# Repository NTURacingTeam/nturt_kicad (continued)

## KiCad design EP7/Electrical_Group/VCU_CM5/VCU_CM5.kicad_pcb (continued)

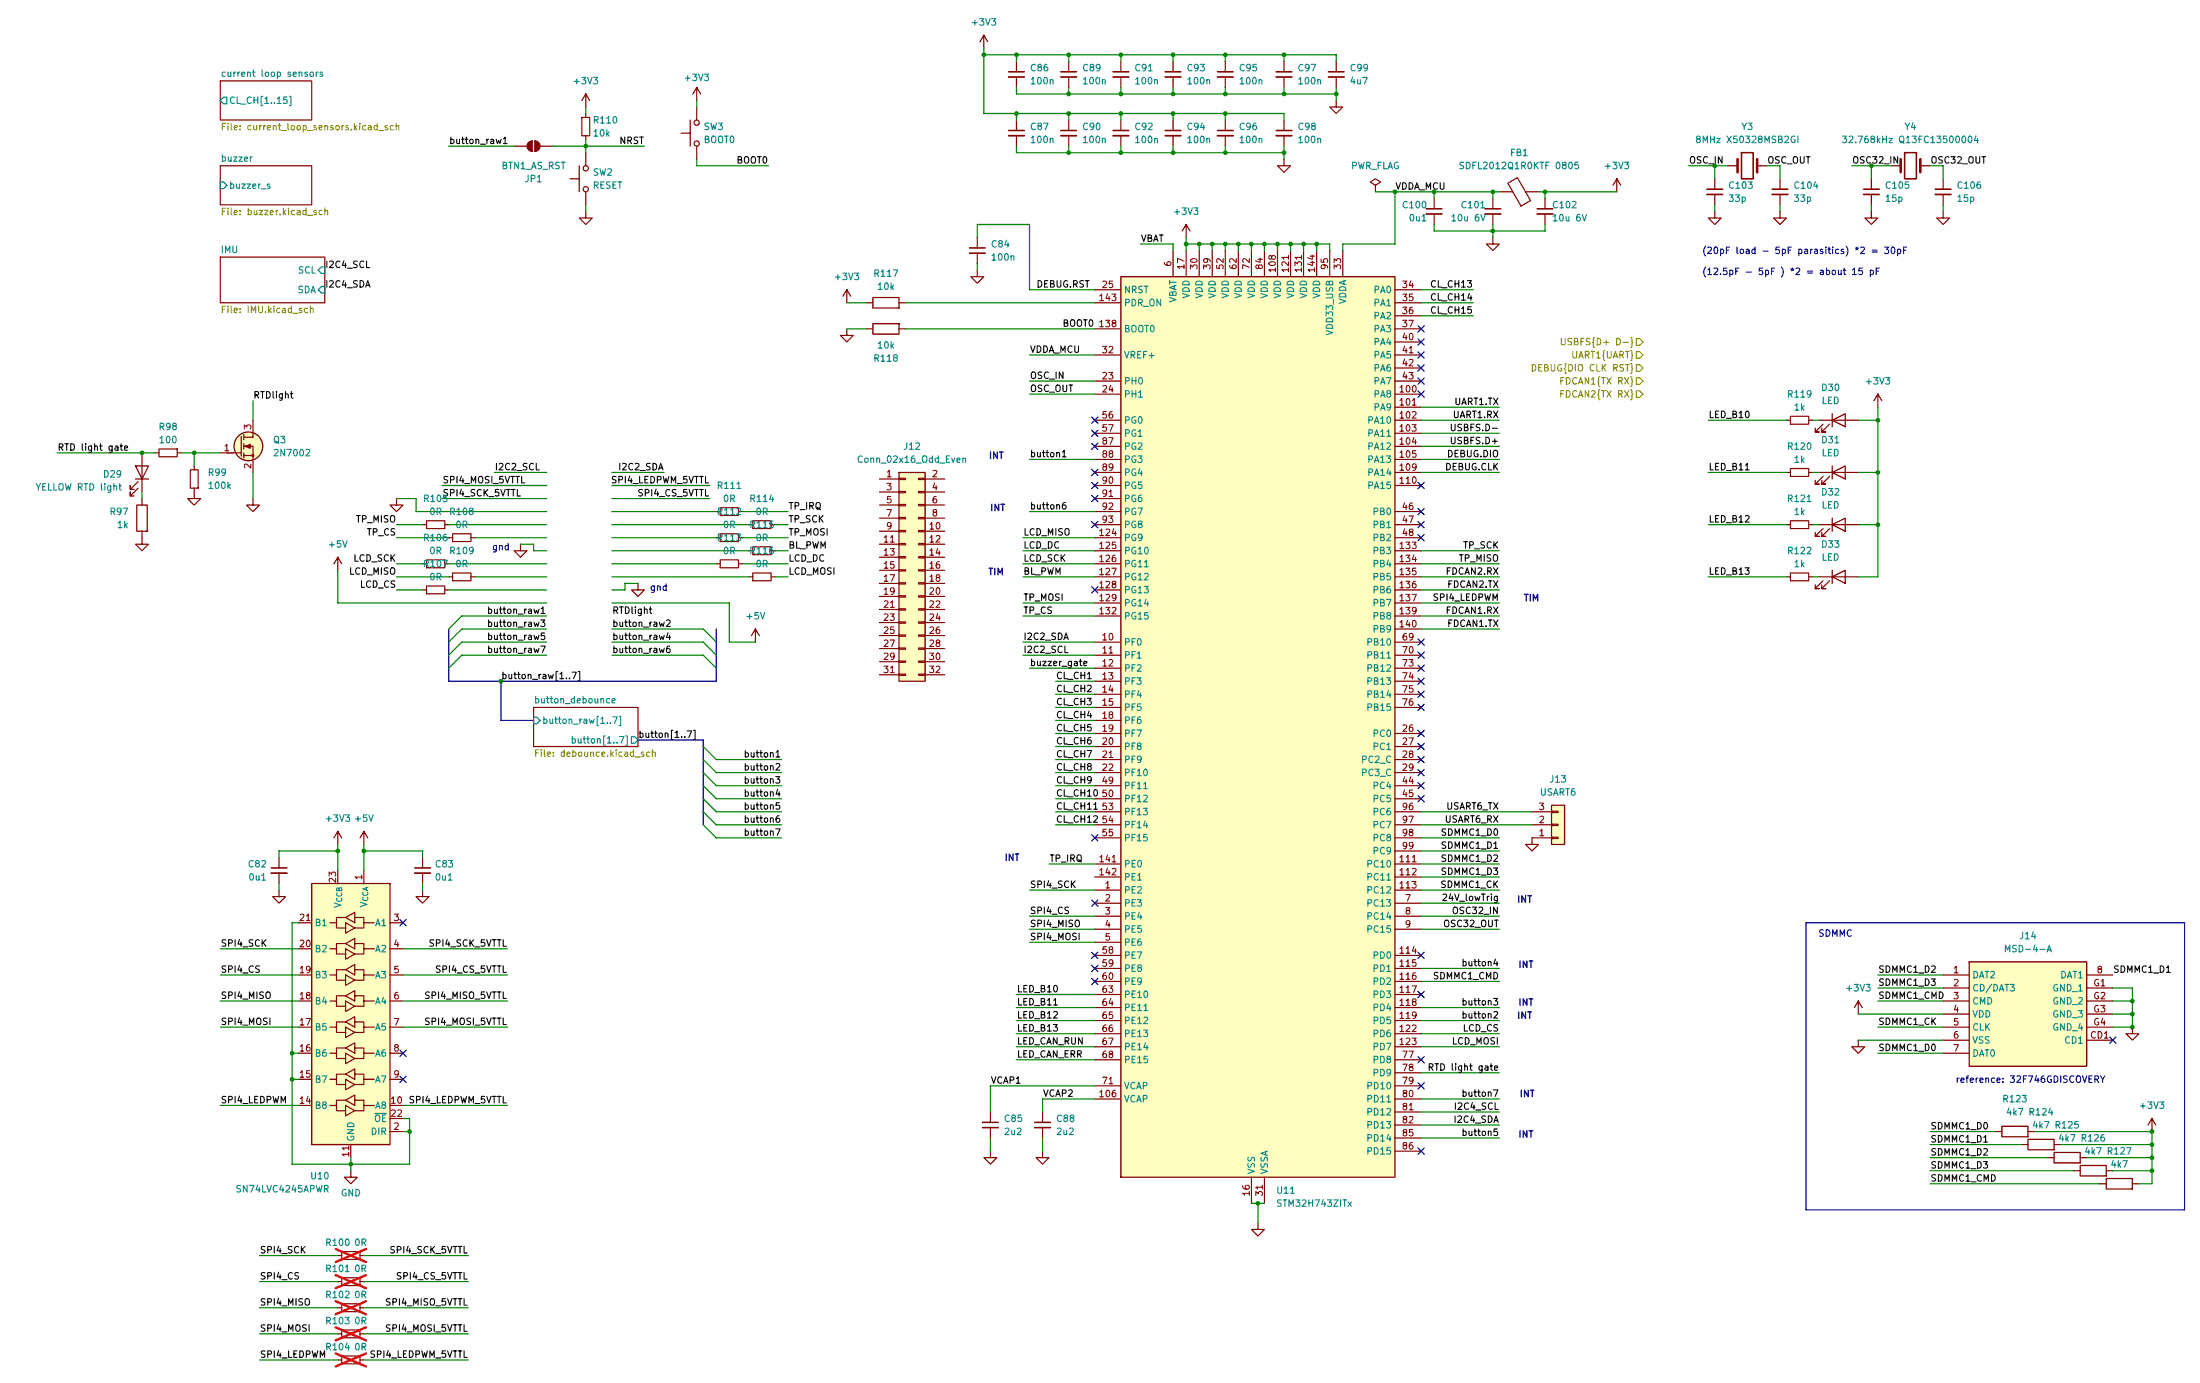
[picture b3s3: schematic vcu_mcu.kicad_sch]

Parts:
C82, C83, C100: 0u1; C_0402_1005Metric
C84, C86, C87, C89, C90, C91, C92, C93, C94, C95, C96, C97, C98: 100n; C_0402_1005Metric
C85, C88: 2u2; C_0402_1005Metric
C99: 4u7; C_0402_1005Metric
C101, C102: 10u 6V; C_0402_1005Metric
C103, C104: 33p; C_0402_1005Metric
C105, C106: 15p; C_0402_1005Metric
D29: YELLOW RTD light; LED_0603_1608Metric
D30, D31, D32, D33: LED; LED_0603_1608Metric
FB1: SDFL2012Q1R0KTF 0805; L_0805_2012Metric
J12: Conn_02x16_Odd_Even; PinSocket_2x16_P2.00mm_Vertical
J13: USART6; JST_PH_B3B-PH-K_1x03_P2.00mm_Vertical
J14: MSD-4-A; MSD4A; Mouser Part Number 179-MSD-4-A
JP1: BTN1_AS_RST; SolderJumper-2_P1.3mm_Open_RoundedPad1.0x1.5mm
Q3: 2N7002; SOT-23
R97, R119, R120, R121, R122: 1k; R_0402_1005Metric
R98: 100; R_0402_1005Metric
R99: 100k; R_0402_1005Metric
R100, R101, R102, R103, R104: 0R; R_0603_1608Metric_Pad0.98x0.95mm_HandSolder; not fitted
R105, R106, R107, R108, R109, R111, R112, R113, R114, R115, R116: 0R; R_0402_1005Metric
R110, R117, R118: 10k; R_0402_1005Metric
R123, R124, R125, R126, R127: 4k7; R_0402_1005Metric
SW2: RESET; SW_Tactile_SPST_NO_Straight_CK_PTS636Sx25SMTRLFS
SW3: BOOT0; SW_Tactile_SPST_NO_Straight_CK_PTS636Sx25SMTRLFS
U10: SN74LVC4245APWR; TSSOP-24_4.4x7.8mm_P0.65mm
U11: STM32H743ZITx; LQFP-144_20x20mm_P0.5mm
Y3: 8MHz X50328MSB2GI; Crystal_SMD_5032-2Pin_5.0x3.2mm
Y4: 32.768kHz Q13FC13500004; Crystal_SMD_3215-2Pin_3.2x1.5mm

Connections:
+3V3: C82.1, C86.1, C87.1, C89.1, C90.1, C91.1, C92.1, C93.1, C94.1, C95.1, C96.1, C97.1, C98.1, C99.1, C102.1, D30.2 (A), D31.2 (A), D32.2 (A), D33.2 (A), FB1.1, J14.4 (VDD), R110.1, R117.1, R123.2, R124.2, R125.2, R126.2, R127.2, SW3.2, U10.23 (V_{CCB}), U10.24 (V_{CCB}), U11.17 (VDD), U11.30 (VDD), U11.39 (VDD), U11.52 (VDD), U11.62 (VDD), U11.72 (VDD), U11.84 (VDD), U11.95 (VDD33_USB), U11.108 (VDD), U11.121 (VDD), U11.131 (VDD), U11.144 (VDD); also elsewhere on the board
+5V: C83.1, U10.1 (V_{CCA}); also elsewhere on the board
/CAN 1/CAN.RX: U11.139 (PB8); also elsewhere on the board
/CAN 1/CAN.TX: U11.140 (PB9); also elsewhere on the board
/CAN 2/CAN.RX: U11.135 (PB5); also elsewhere on the board
/CAN 2/CAN.TX: U11.136 (PB6); also elsewhere on the board
/DFP1.D+: U11.104 (PA12); also elsewhere on the board
/DFP1.D-: U11.103 (PA11); also elsewhere on the board
/stlink/DEBUG.CLK: U11.109 (PA14); also elsewhere on the board
/stlink/DEBUG.DIO: U11.105 (PA13); also elsewhere on the board
/stlink/DEBUG.RST: C84.1, U11.25 (NRST); also elsewhere on the board
/stlink/VCP_MCU.RX: U11.102 (PA10); also elsewhere on the board
/stlink/VCP_MCU.TX: U11.101 (PA9); also elsewhere on the board
/vcu mcu/24V_lowTrig: U11.7 (PC13)
/vcu mcu/BL_PWM: R115.2, U11.127 (PG12)
/vcu mcu/BOOT0: R118.2, SW3.1, U11.138 (BOOT0)
/vcu mcu/I2C2_SCL: U11.11 (PF1)
/vcu mcu/I2C2_SDA: U11.10 (PF0)
/vcu mcu/I2C4_SCL: U11.81 (PD12); also elsewhere on the board
/vcu mcu/I2C4_SDA: U11.82 (PD13); also elsewhere on the board
/vcu mcu/LCD_CS: R107.1, U11.122 (PD6)
/vcu mcu/LCD_DC: R113.2, U11.125 (PG10)
/vcu mcu/LCD_MISO: R109.1, U11.124 (PG9)
/vcu mcu/LCD_MOSI: R116.2, U11.123 (PD7)
/vcu mcu/LCD_SCK: R106.1, U11.126 (PG11)
/vcu mcu/LED_B10: R119.1, U11.63 (PE10)
/vcu mcu/LED_B11: R120.1, U11.64 (PE11)
/vcu mcu/LED_B12: R121.1, U11.65 (PE12)
/vcu mcu/LED_B13: R122.1, U11.66 (PE13)
/vcu mcu/LED_CAN_ERR: U11.68 (PE15)
/vcu mcu/LED_CAN_RUN: U11.67 (PE14)
/vcu mcu/NRST: JP1.1 (A), R110.2, SW2.2
/vcu mcu/OSC32_IN: C105.1, U11.8 (PC14), Y4.1
/vcu mcu/OSC32_OUT: C106.1, U11.9 (PC15), Y4.2
/vcu mcu/OSC_IN: C103.1, U11.23 (PH0), Y3.1
/vcu mcu/OSC_OUT: C104.1, U11.24 (PH1), Y3.2
/vcu mcu/RTD light gate: D29.2 (A), R98.2, U11.78 (PD9)
/vcu mcu/RTDlight: Q3.3 (D)
/vcu mcu/SDMMC1_CK: J14.5 (CLK), U11.113 (PC12)
/vcu mcu/SDMMC1_CMD: J14.3 (CMD), R127.1, U11.116 (PD2)
/vcu mcu/SDMMC1_D0: J14.7 (DAT0), R123.1, U11.98 (PC8)
/vcu mcu/SDMMC1_D1: J14.8 (DAT1), R124.1, U11.99 (PC9)
/vcu mcu/SDMMC1_D2: J14.1 (DAT2), R125.1, U11.111 (PC10)
/vcu mcu/SDMMC1_D3: J14.2 (CD/DAT3), R126.1, U11.112 (PC11)
/vcu mcu/SPI4_CS: R101.1, U10.19 (B3), U11.3 (PE4)
/vcu mcu/SPI4_CS_5VTTL: R101.2, U10.5 (A3)
/vcu mcu/SPI4_LEDPWM: R104.1, U10.14 (B8), U11.137 (PB7)
/vcu mcu/SPI4_LEDPWM_5VTTL: R104.2, U10.10 (A8)
/vcu mcu/SPI4_MISO: R102.1, U10.18 (B4), U11.4 (PE5)
/vcu mcu/SPI4_MISO_5VTTL: R102.2, U10.6 (A4)
/vcu mcu/SPI4_MOSI: R103.1, U10.17 (B5), U11.5 (PE6)
/vcu mcu/SPI4_MOSI_5VTTL: R103.2, U10.7 (A5)
/vcu mcu/SPI4_SCK: R100.1, U10.20 (B2), U11.1 (PE2)
/vcu mcu/SPI4_SCK_5VTTL: R100.2, U10.4 (A2)
/vcu mcu/TP_CS: R108.1, U11.132 (PG15)
/vcu mcu/TP_IRQ: R111.1, U11.141 (PE0)
/vcu mcu/TP_MISO: R105.1, U11.134 (PB4)
/vcu mcu/TP_MOSI: R112.2, U11.129 (PG14)
/vcu mcu/TP_SCK: R114.2, U11.133 (PB3)
/vcu mcu/USART6_RX: J13.2, U11.97 (PC7)
/vcu mcu/USART6_TX: J13.3, U11.96 (PC6)
/vcu mcu/VBAT: U11.6 (VBAT)
/vcu mcu/VCAP1: C85.1, U11.71 (VCAP)
/vcu mcu/VCAP2: C88.1, U11.106 (VCAP)
/vcu mcu/VDDA_MCU: C100.1, C101.1, FB1.2, U11.32 (VREF+), U11.33 (VDDA)
/vcu mcu/button1: U11.88 (PG3); also elsewhere on the board
/vcu mcu/button2: U11.119 (PD5); also elsewhere on the board
/vcu mcu/button3: U11.118 (PD4); also elsewhere on the board
/vcu mcu/button4: U11.115 (PD1); also elsewhere on the board
/vcu mcu/button5: U11.85 (PD14); also elsewhere on the board
/vcu mcu/button6: U11.92 (PG7); also elsewhere on the board
/vcu mcu/button7: U11.80 (PD11); also elsewhere on the board
/vcu mcu/button_raw1: JP1.2 (B); also elsewhere on the board
/vcu mcu/buzzer_gate: U11.12 (PF2)
/vcu mcu/current loop sensors/CL_CH1: U11.13 (PF3); also elsewhere on the board
/vcu mcu/current loop sensors/CL_CH2: U11.14 (PF4); also elsewhere on the board
/vcu mcu/current loop sensors/CL_CH3: U11.15 (PF5); also elsewhere on the board
/vcu mcu/current loop sensors/CL_CH4: U11.18 (PF6); also elsewhere on the board
/vcu mcu/current loop sensors/CL_CH5: U11.19 (PF7); also elsewhere on the board
/vcu mcu/current loop sensors/CL_CH6: U11.20 (PF8); also elsewhere on the board
/vcu mcu/current loop sensors/CL_CH7: U11.21 (PF9); also elsewhere on the board
/vcu mcu/current loop sensors/CL_CH8: U11.22 (PF10); also elsewhere on the board
/vcu mcu/current loop sensors/CL_CH9: U11.49 (PF11); also elsewhere on the board
/vcu mcu/current loop sensors/CL_CH10: U11.50 (PF12); also elsewhere on the board
/vcu mcu/current loop sensors/CL_CH11: U11.53 (PF13); also elsewhere on the board
/vcu mcu/current loop sensors/CL_CH12: U11.54 (PF14); also elsewhere on the board
/vcu mcu/current loop sensors/CL_CH13: U11.34 (PA0); also elsewhere on the board
/vcu mcu/current loop sensors/CL_CH14: U11.35 (PA1); also elsewhere on the board
/vcu mcu/current loop sensors/CL_CH15: U11.36 (PA2); also elsewhere on the board
GND: C82.2, C83.2, C84.2, C85.2, C86.2, C87.2, C88.2, C89.2, C90.2, C91.2, C92.2, C93.2, C94.2, C95.2, C96.2, C97.2, C98.2, C99.2, C100.2, C101.2, C102.2, C103.2, C104.2, C105.2, C106.2, J13.1, J14.6 (VSS), J14.G1 (GND_1), J14.G2 (GND_2), J14.G3 (GND_3), J14.G4 (GND_4), Q3.2 (S), R97.2, R99.1, R118.1, SW2.1, U10.2 (DIR), U10.11 (GND), U10.12 (GND), U10.13 (GND), U10.15 (B7), U10.16 (B6), U10.21 (B1), U10.22 (~OE), U11.16 (VSS), U11.31 (VSSA), U11.38 (VSS), U11.51 (VSS), U11.61 (VSS), U11.83 (VSS), U11.94 (VSS), U11.107 (VSS), U11.120 (VSS), U11.130 (VSS); also elsewhere on the board
unnamed: D29.1 (K), R97.1
unnamed: D30.1 (K), R119.2
unnamed: D31.1 (K), R120.2
unnamed: D32.1 (K), R121.2
unnamed: D33.1 (K), R122.2
unnamed: Q3.1 (G), R98.1, R99.2
unnamed: R117.2, U11.143 (PDR_ON)

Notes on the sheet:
gnd
SDMMC
TIM
(20pF load - 5pF parasitics) *2 = 30pF (12.5pF - 5pF ) *2 = about 15 pF
INT
reference: 32F746GDISCOVERY

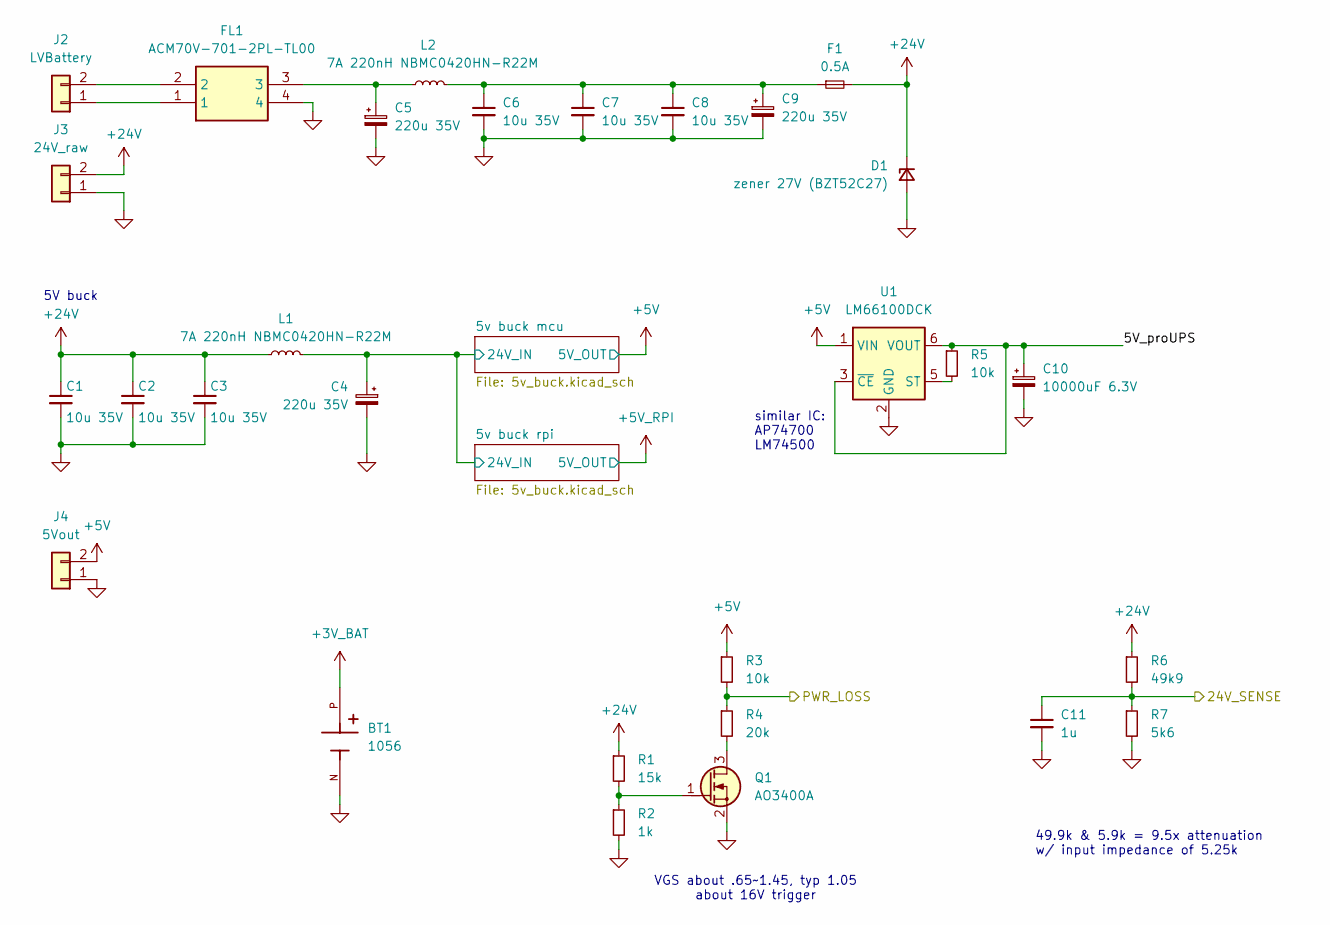
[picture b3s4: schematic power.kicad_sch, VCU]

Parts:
BT1: 1056; BAT_1056; PARTREV D
C1, C2, C3, C6, C7, C8: 10u 35V; C_1206_3216Metric
C4, C5, C9: 220u 35V; CP_Radial_D8.0mm_P3.80mm
C10: 10000uF 6.3V; CP_Radial_D10.0mm_P5.00mm
C11: 1u; C_0402_1005Metric
D1: zener 27V (BZT52C27); D_SOD-123
F1: 0.5A; Fuse_1206_3216Metric
FL1: ACM70V-701-2PL-TL00; Common_Mode_Choke_4A_ACM70V7012PLTL00; Mouser Part Number 810-ACM70V7012PLTL00
J2: LVBattery; JST_XH_B2B-XH-A_1x02_P2.50mm_Vertical
J3: 24V_raw; JST_XH_B2B-XH-A_1x02_P2.50mm_Vertical
J4: 5Vout; JST_XH_B2B-XH-A_1x02_P2.50mm_Vertical
L1, L2: 7A 220nH NBMC0420HN-R22M; L_Ferrocore_DLG-0403
Q1: AO3400A; SOT-23
R1: 15k; R_0402_1005Metric
R2: 1k; R_0402_1005Metric
R3, R5: 10k; R_0402_1005Metric
R4: 20k; R_0402_1005Metric
R6: 49k9; R_0402_1005Metric
R7: 5k6; R_0402_1005Metric
U1: LM66100DCK; SOT-363_SC-70-6

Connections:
+3V_BAT: BT1.P; also elsewhere on the board
+5V: J4.2, R3.1, U1.1 (VIN); also elsewhere on the board
+24V: C1.1, C2.1, C3.1, D1.1 (K), F1.2, J3.2, L1.1, R1.1, R6.1; also elsewhere on the board
/power/5V_proUPS: C10.1, R5.1, U1.3 (~CE), U1.6 (VOUT)
/power/5v buck mcu/24V_IN: C4.1, L1.2; also elsewhere on the board
/power/24V_SENSE: C11.1, R6.2, R7.1
/power/PWR_LOSS: R3.2, R4.1
GND: BT1.N, C1.2, C2.2, C3.2, C4.2, C5.2, C6.2, C7.2, C8.2, C9.2, C10.2, C11.2, D1.2 (A), FL1.4, J3.1, J4.1, Q1.2 (S), R2.2, R7.2, U1.2 (GND); also elsewhere on the board
unnamed: C5.1, FL1.3, L2.1
unnamed: C6.1, C7.1, C8.1, C9.1, F1.1, L2.2
unnamed: FL1.1, J2.1
unnamed: FL1.2, J2.2
unnamed: Q1.3 (D), R4.2
unnamed: Q1.1 (G), R1.2, R2.1
unnamed: R5.2, U1.5 (ST)

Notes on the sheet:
similar IC: AP74700 LM74500
5V buck
49.9k & 5.9k = 9.5x attenuation w/ input impedance of 5.25k
VGS about .65~1.45, typ 1.05 about 16V trigger

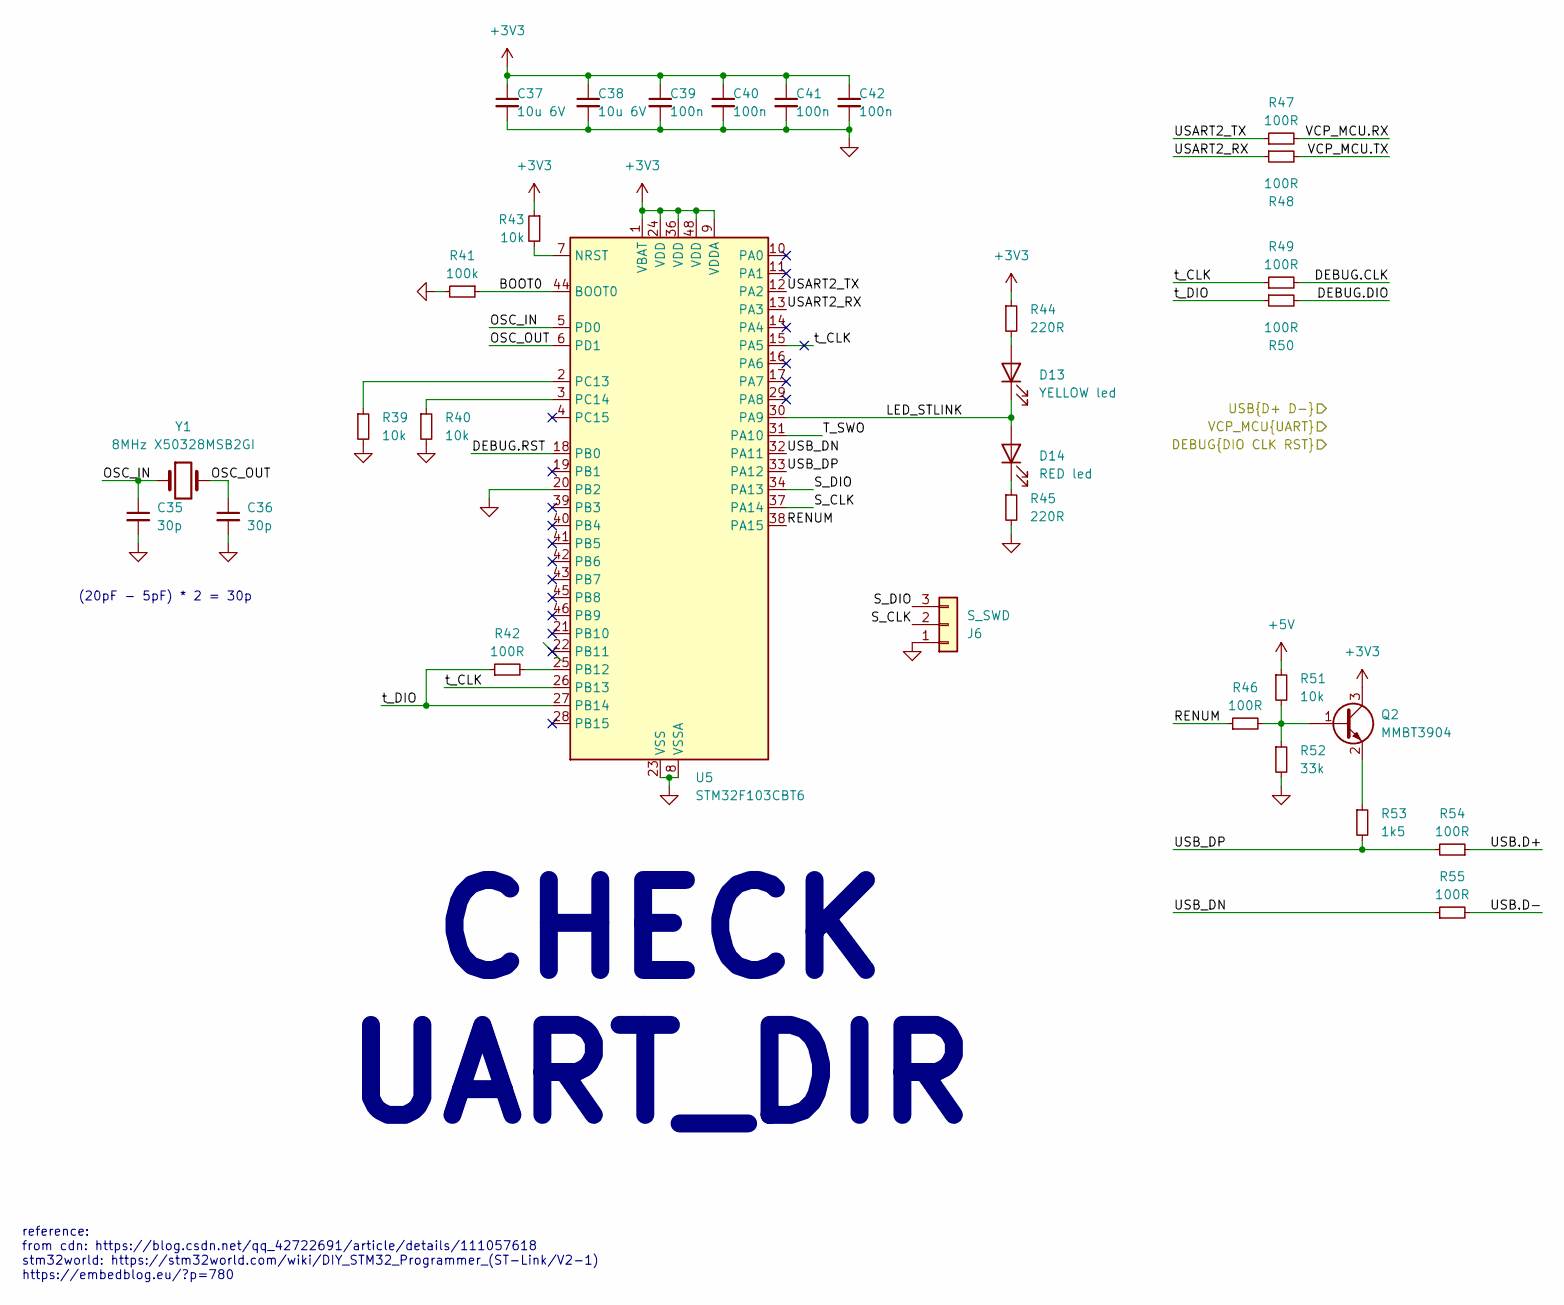
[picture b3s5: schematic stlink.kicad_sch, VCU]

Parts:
C35, C36: 30p; C_0402_1005Metric
C37, C38: 10u 6V; C_0402_1005Metric
C39, C40, C41, C42: 100n; C_0402_1005Metric
D13: YELLOW led; LED_0603_1608Metric
D14: RED led; LED_0603_1608Metric
J6: S_SWD; PinHeader_1x03_P2.54mm_Vertical
Q2: MMBT3904; SOT-23
R39, R40, R43, R51: 10k; R_0402_1005Metric
R41: 100k; R_0402_1005Metric
R42, R46, R47, R48, R49, R50, R54, R55: 100R; R_0402_1005Metric
R44, R45: 220R; R_0402_1005Metric
R52: 33k; R_0402_1005Metric
R53: 1k5; R_0402_1005Metric
U5: STM32F103CBT6; LQFP-48_7x7mm_P0.5mm
Y1: 8MHz X50328MSB2GI; Crystal_SMD_5032-2Pin_5.0x3.2mm

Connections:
+3V3: C37.1, C38.1, C39.1, C40.1, C41.1, C42.1, Q2.3 (C), R43.1, R44.1, U5.1 (VBAT), U5.9 (VDDA), U5.24 (VDD), U5.36 (VDD), U5.48 (VDD); also elsewhere on the board
+5V: R51.1; also elsewhere on the board
/DFP0.D+: R54.1; also elsewhere on the board
/DFP0.D-: R55.2; also elsewhere on the board
/stlink/BOOT0: R41.1, U5.44 (BOOT0)
/stlink/DEBUG.CLK: R49.2; also elsewhere on the board
/stlink/DEBUG.DIO: R50.2; also elsewhere on the board
/stlink/DEBUG.RST: U5.18 (PB0); also elsewhere on the board
/stlink/LED_STLINK: D13.1 (K), D14.2 (A), U5.30 (PA9)
/stlink/OSC_IN: C35.1, U5.5 (PD0), Y1.1
/stlink/OSC_OUT: C36.1, U5.6 (PD1), Y1.2
/stlink/RENUM: R46.1, U5.38 (PA15)
/stlink/S_CLK: J6.2, U5.37 (PA14)
/stlink/S_DIO: J6.3, U5.34 (PA13)
/stlink/T_SWO: U5.31 (PA10)
/stlink/USART2_RX: R48.1, U5.13 (PA3)
/stlink/USART2_TX: R47.1, U5.12 (PA2)
/stlink/USB_DN: R55.1, U5.32 (PA11)
/stlink/USB_DP: R53.2, R54.2, U5.33 (PA12)
/stlink/VCP_MCU.RX: R47.2; also elsewhere on the board
/stlink/VCP_MCU.TX: R48.2; also elsewhere on the board
/stlink/t_CLK: R49.1, U5.15 (PA5), U5.26 (PB13)
/stlink/t_DIO: R42.1, R50.1, U5.27 (PB14)
GND: C35.2, C36.2, C37.2, C38.2, C39.2, C40.2, C41.2, C42.2, J6.1, R39.2, R40.2, R41.2, R45.2, R52.2, U5.8 (VSSA), U5.20 (PB2), U5.23 (VSS), U5.35 (VSS), U5.47 (VSS); also elsewhere on the board
unnamed: D13.2 (A), R44.2
unnamed: D14.1 (K), R45.1
unnamed: Q2.1 (B), R46.2, R51.2, R52.1
unnamed: Q2.2 (E), R53.1
unnamed: R43.2, U5.7 (NRST)
unnamed: R42.2, U5.25 (PB12)
unnamed: R39.1, U5.2 (PC13)
unnamed: R40.1, U5.3 (PC14)

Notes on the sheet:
(20pF - 5pF) * 2 = 30p
reference: from cdn: https://blog.csdn.net/qq_42722691/article/details/111057618 stm32world: https://stm32world.com/wiki/DIY_STM32_Programmer_(ST-Link/V2-1) https://embedblog.eu/?p=780
CHECK UART_DIR

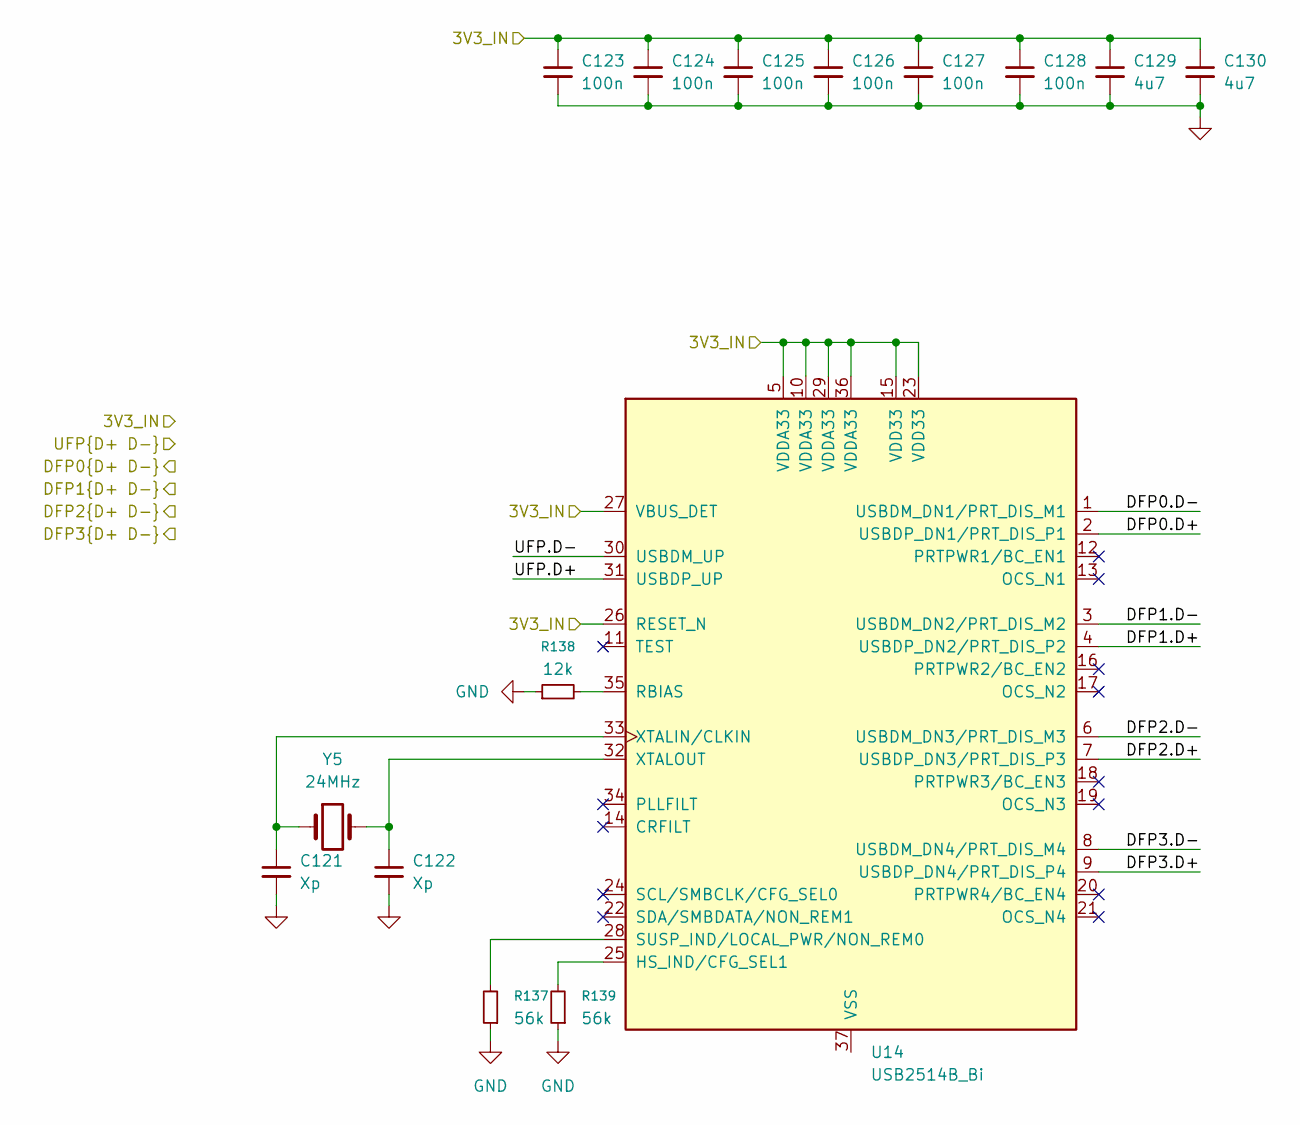
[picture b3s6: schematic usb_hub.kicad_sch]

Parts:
C121, C122: Xp; C_0402_1005Metric
C123, C124, C125, C126, C127, C128: 100n; C_0402_1005Metric
C129, C130: 4u7; C_0402_1005Metric
R137, R139: 56k; R_0402_1005Metric
R138: 12k; R_0402_1005Metric
U14: USB2514B_Bi; QFN-36-1EP_6x6mm_P0.5mm_EP3.7x3.7mm
Y5: 24MHz; Crystal_SMD_5032-2Pin_5.0x3.2mm

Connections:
/DFP0.D+: U14.2 (USBDP_DN1/PRT_DIS_P1); also elsewhere on the board
/DFP0.D-: U14.1 (USBDM_DN1/PRT_DIS_M1); also elsewhere on the board
/DFP1.D+: U14.4 (USBDP_DN2/PRT_DIS_P2); also elsewhere on the board
/DFP1.D-: U14.3 (USBDM_DN2/PRT_DIS_M2); also elsewhere on the board
/DFP2.D+: U14.7 (USBDP_DN3/PRT_DIS_P3)
/DFP2.D-: U14.6 (USBDM_DN3/PRT_DIS_M3)
/DFP3.D+: U14.9 (USBDP_DN4/PRT_DIS_P4)
/DFP3.D-: U14.8 (USBDM_DN4/PRT_DIS_M4)
/computer/3V3_CAM: C123.1, C124.1, C125.1, C126.1, C127.1, C128.1, C129.1, C130.1, U14.5 (VDDA33), U14.10 (VDDA33), U14.15 (VDD33), U14.23 (VDD33), U14.26 (RESET_N), U14.27 (VBUS_DET), U14.29 (VDDA33), U14.36 (VDDA33); also elsewhere on the board
/computer/USB3_0.D+: U14.31 (USBDP_UP); also elsewhere on the board
/computer/USB3_0.D-: U14.30 (USBDM_UP); also elsewhere on the board
GND: C121.2, C122.2, C123.2, C124.2, C125.2, C126.2, C127.2, C128.2, C129.2, C130.2, R137.1, R138.1, R139.1; also elsewhere on the board
unnamed: R139.2, U14.25 (HS_IND/CFG_SEL1)
unnamed: R138.2, U14.35 (RBIAS)
unnamed: R137.2, U14.28 (SUSP_IND/LOCAL_PWR/NON_REM0)
unnamed: C121.1, U14.33 (XTALIN/CLKIN), Y5.1
unnamed: C122.1, U14.32 (XTALOUT), Y5.2
